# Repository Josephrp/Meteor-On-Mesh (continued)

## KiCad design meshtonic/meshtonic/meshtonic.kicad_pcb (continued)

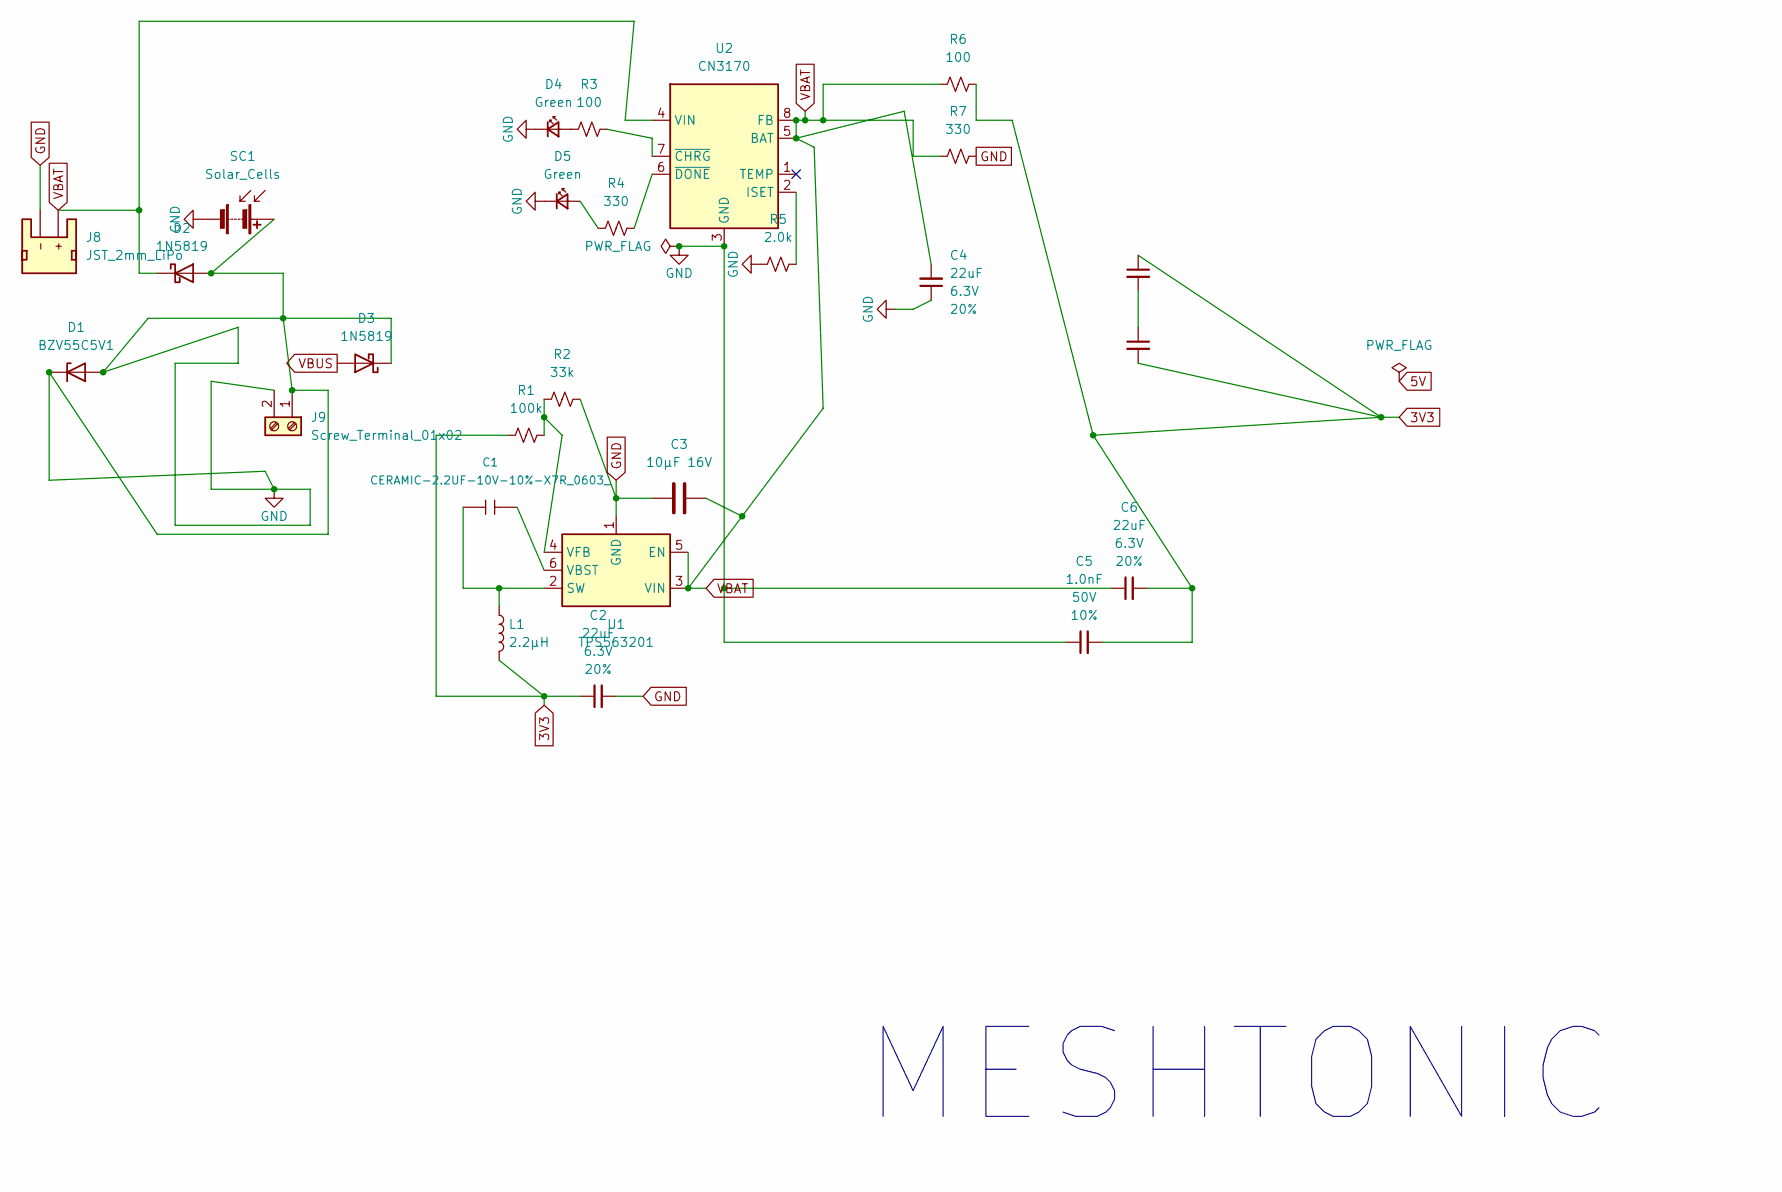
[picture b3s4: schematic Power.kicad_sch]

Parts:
C1: CERAMIC-2.2UF-10V-10%-X7R_0603_; C_0603_1608Metric; MPN CC0603KRX7R6BB225
C2, C4, C6, C7: 22uF; C_0603_1608Metric; Voltage 6.3V; Tolerance 20%
C3: 10µF 16V; C_0603_1608Metric
C5, C8: 1.0nF; C_0603_1608Metric; Voltage 50V; Tolerance 10%
D1: BZV55C5V1; D_MiniMELF
D2, D3: 1N5819; D_DO-41_SOD81_P10.16mm_Horizontal
D4, D5: Green; LED_1206_3216Metric_Green
J8: JST_2mm_LiPo; JST_1x02_P2.0mm_Horizontal_SMD
J9: Screw_Terminal_01x02; PinHeader_1x02_P2.54mm_Vertical
L1: 2.2µH; L_6.3x6.3_H3
R1: 100k; R_0402_1005Metric
R2: 33k; R_0402_1005Metric
R3, R6: 100; R_0402_1005Metric
R4, R7: 330; R_0603_1608Metric
R5: 2.0k; R_0402_1005Metric
SC1: Solar_Cells; PinHeader_1x02_P2.54mm_Vertical
U1: TPS563201; SOT-23-6
U2: CN3170; SOIC-8-1EP_3.9x4.9mm_P1.27mm_EP2.41x3.3mm_ThermalVias

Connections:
3V3: C2.1, C5.2, C6.2, C7.1, C8.2, L1.2, R1.1, R6.2; also elsewhere on the board
GND: C2.2, C3.1, C4.1, C5.1, C6.1, D1.1 (K), D1.2 (A), D2.2 (A), D3.1 (K), D4.1 (K), D5.1 (K), J8.1 (-), J9.1, J9.2, R2.2, R5.1, R7.2, SC1.1 (+), SC1.2 (-), U1.1 (GND), U2.3 (GND), U2.9 (GND); also elsewhere on the board
unnamed: C7.2, C8.1
unnamed: D4.2 (A), R3.1
unnamed: D5.2 (A), R4.1
unnamed: C1.2, L1.1, U1.2 (SW)
unnamed: C1.1, U1.6 (VBST)
unnamed: R1.2, R2.1, U1.4 (VFB)
unnamed: R5.2, U2.2 (ISET)
unnamed: R3.2, U2.7 (~CHRG)
unnamed: R4.2, U2.6 (~DONE)
VBAT: C3.2, C4.2, D2.1 (K), J8.2 (+), R6.1, R7.1, U1.3 (VIN), U1.5 (EN), U2.4 (VIN), U2.5 (BAT), U2.8 (FB); also elsewhere on the board
VBUS: D3.2 (A); also elsewhere on the board

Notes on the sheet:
MESHTONIC

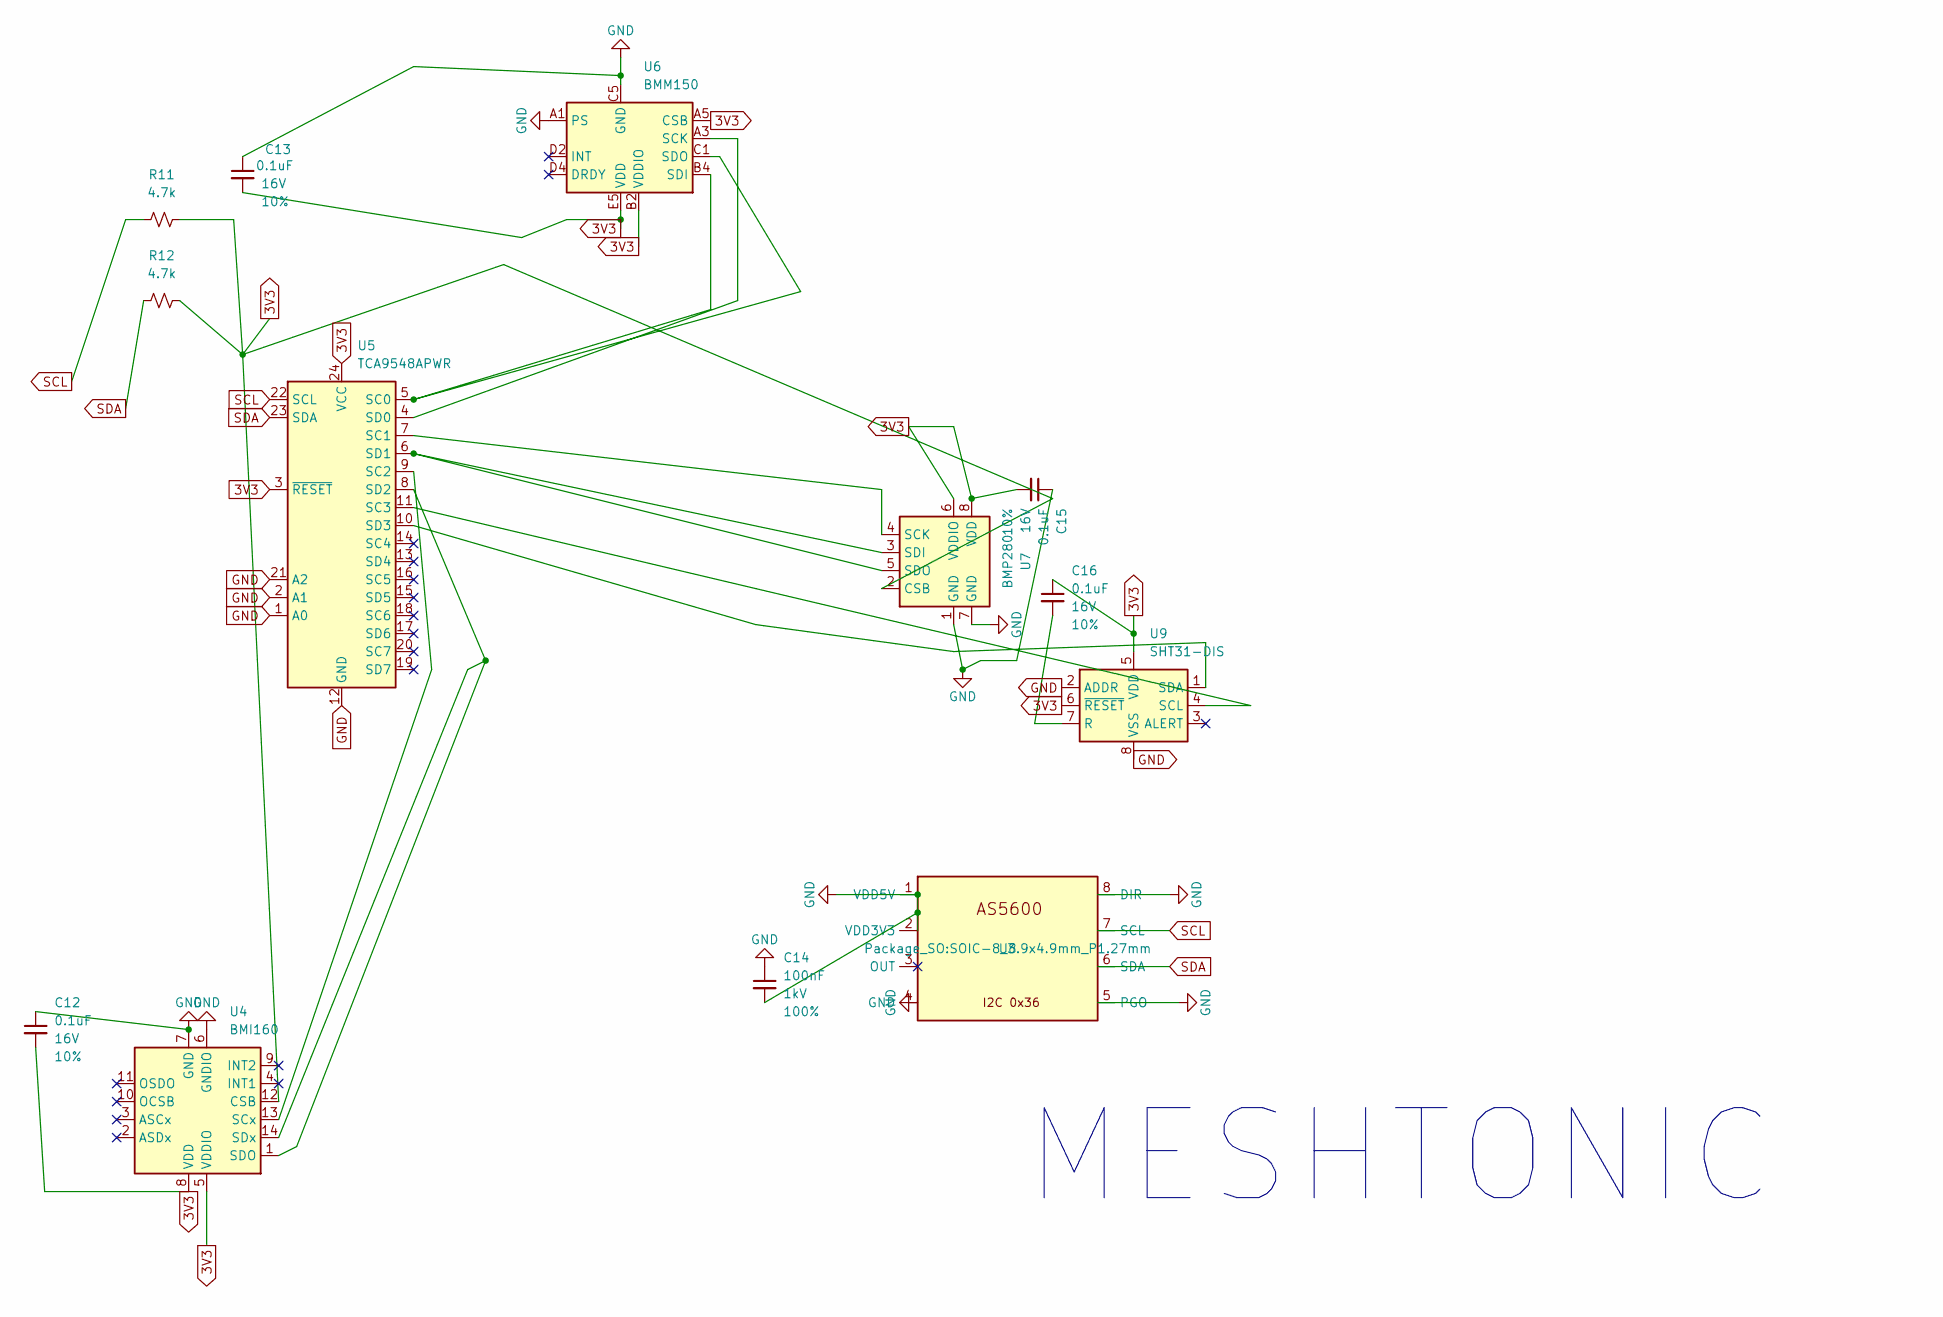
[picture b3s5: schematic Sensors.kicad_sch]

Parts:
C12, C13, C15, C16: 0.1uF; C_0402_1005Metric; Voltage 16V; Tolerance 10%
C14: 100nF; C_0603_1608Metric; Voltage 1kV; Tolerance 100%
R11, R12: 4.7k; R_0402_1005Metric
U4: BMI160; Bosch_LGA-14_3x2.5mm_P0.5mm
U5: TCA9548APWR; TSSOP-24_4.4x7.8mm_P0.65mm
U6: BMM150; WLCSP-12_1.56x1.56mm_P0.4mm
U7: BMP280; Bosch_LGA-8_2x2.5mm_P0.65mm_ClockwisePinNumbering
U8: Package_SO:SOIC-8_3.9x4.9mm_P1.27mm; SOIC-8_3.9x4.9mm_P1.27mm
U9: SHT31-DIS; Sensirion_DFN-8-1EP_2.5x2.5mm_P0.5mm_EP1.1x1.7mm

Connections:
3V3: C12.2, C13.2, C15.2, C16.1, R11.2, R12.2, U4.5 (VDDIO), U4.8 (VDD), U4.12 (CSB), U5.3 (~RESET), U5.24 (VCC), U6.A5 (CSB), U6.B2 (VDDIO), U6.E5 (VDD), U7.2 (CSB), U7.6 (VDDIO), U7.8 (VDD), U9.5 (VDD), U9.6 (~RESET); also elsewhere on the board
GND: C12.1, C13.1, C14.1, C14.2, C15.1, U4.6 (GNDIO), U4.7 (GND), U5.1 (A0), U5.2 (A1), U5.12 (GND), U5.21 (A2), U6.A1 (PS), U6.C5 (GND), U6.E1 (GND), U6.E3 (GND), U7.1 (GND), U7.7 (GND), U8.1 (VDD5V), U8.2 (VDD3V3), U8.4 (GND), U8.5 (PGO), U8.8 (DIR), U9.2 (ADDR), U9.8 (VSS), U9.9 (VSS); also elsewhere on the board
unnamed: U4.13 (SCx), U5.9 (SC2)
unnamed: U4.1 (SDO), U4.14 (SDx), U5.8 (SD2)
unnamed: U5.5 (SC0), U6.B4 (SDI), U6.C1 (SDO)
unnamed: U5.7 (SC1), U7.4 (SCK)
unnamed: U5.11 (SC3), U9.4 (SCL)
unnamed: U5.4 (SD0), U6.A3 (SCK)
unnamed: U5.6 (SD1), U7.3 (SDI), U7.5 (SDO)
unnamed: U5.10 (SD3), U9.1 (SDA)
unnamed: C16.2, U9.7 (R)
SCL: R11.1, U5.22 (SCL), U8.7 (SCL); also elsewhere on the board
SDA: R12.1, U5.23 (SDA), U8.6 (SDA); also elsewhere on the board

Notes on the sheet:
MESHTONIC

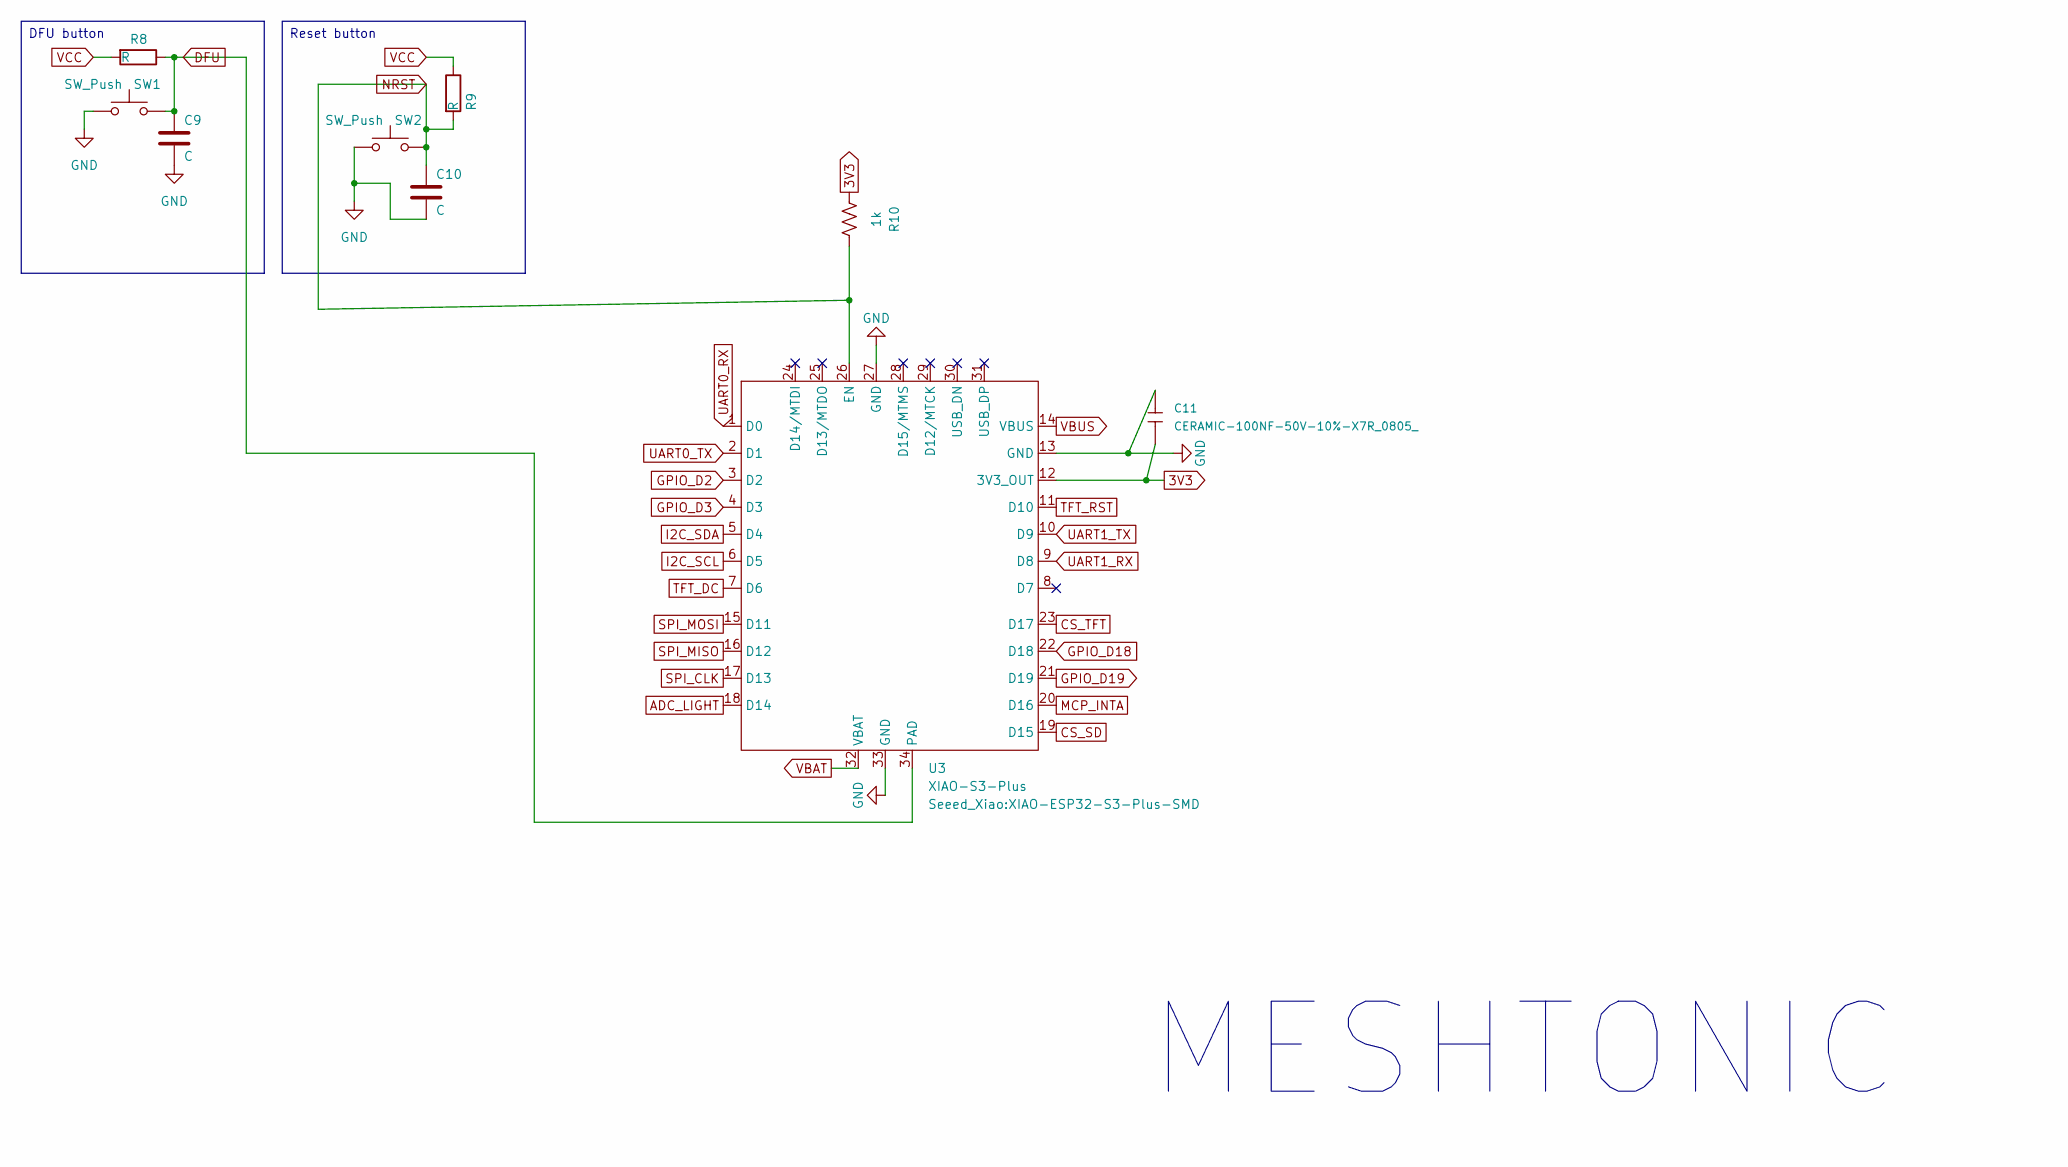
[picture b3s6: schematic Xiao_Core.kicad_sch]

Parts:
C9, C10: C; C_0402_1005Metric; Part CL05B104KO5NNNC; JLC 0402
C11: CERAMIC-100NF-50V-10%-X7R_0805_; C_0603_1608Metric; MPN CC0805KRX7R9BB104
R8, R9: R; R_0603_1608Metric; Part 0603WAF1103T5E; JLC 0603
R10: 1k; R_0603_1608Metric
SW1, SW2: SW_Push; SW_Push_1P1T_XKB_TS-1187A; Part TS-1187A-B-A-B; JLC SMD
U3: XIAO-S3-Plus; XIAO-ESP32-S3-Plus-SMD

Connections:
3V3: C11.2, R10.2, U3.12 (3V3_OUT); also elsewhere on the board
ADC_LIGHT: U3.18 (D14); also elsewhere on the board
CS_SD: U3.19 (D15); also elsewhere on the board
CS_TFT: U3.23 (D17); also elsewhere on the board
DFU: C9.1, R8.1, SW1.2, U3.34 (PAD)
GND: C9.2, C10.2, C11.1, SW1.1, SW2.1, U3.13 (GND), U3.27 (GND), U3.33 (GND); also elsewhere on the board
GPIO_D2: U3.3 (D2); also elsewhere on the board
GPIO_D3: U3.4 (D3); also elsewhere on the board
GPIO_D18: U3.22 (D18); also elsewhere on the board
GPIO_D19: U3.21 (D19); also elsewhere on the board
I2C_SCL: U3.6 (D5); also elsewhere on the board
I2C_SDA: U3.5 (D4); also elsewhere on the board
MCP_INTA: U3.20 (D16); also elsewhere on the board
NRST: C10.1, R9.2, R10.1, SW2.2, U3.26 (EN)
SPI_CLK: U3.17 (D13); also elsewhere on the board
SPI_MISO: U3.16 (D12); also elsewhere on the board
SPI_MOSI: U3.15 (D11); also elsewhere on the board
TFT_DC: U3.7 (D6); also elsewhere on the board
TFT_RST: U3.11 (D10); also elsewhere on the board
UART0_RX: U3.1 (D0); also elsewhere on the board
UART0_TX: U3.2 (D1); also elsewhere on the board
UART1_RX: U3.9 (D8); also elsewhere on the board
UART1_TX: U3.10 (D9); also elsewhere on the board
VBAT: U3.32 (VBAT); also elsewhere on the board
VBUS: U3.14 (VBUS); also elsewhere on the board
VCC: R8.2, R9.1

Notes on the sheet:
MESHTONIC
DFU button
Reset button

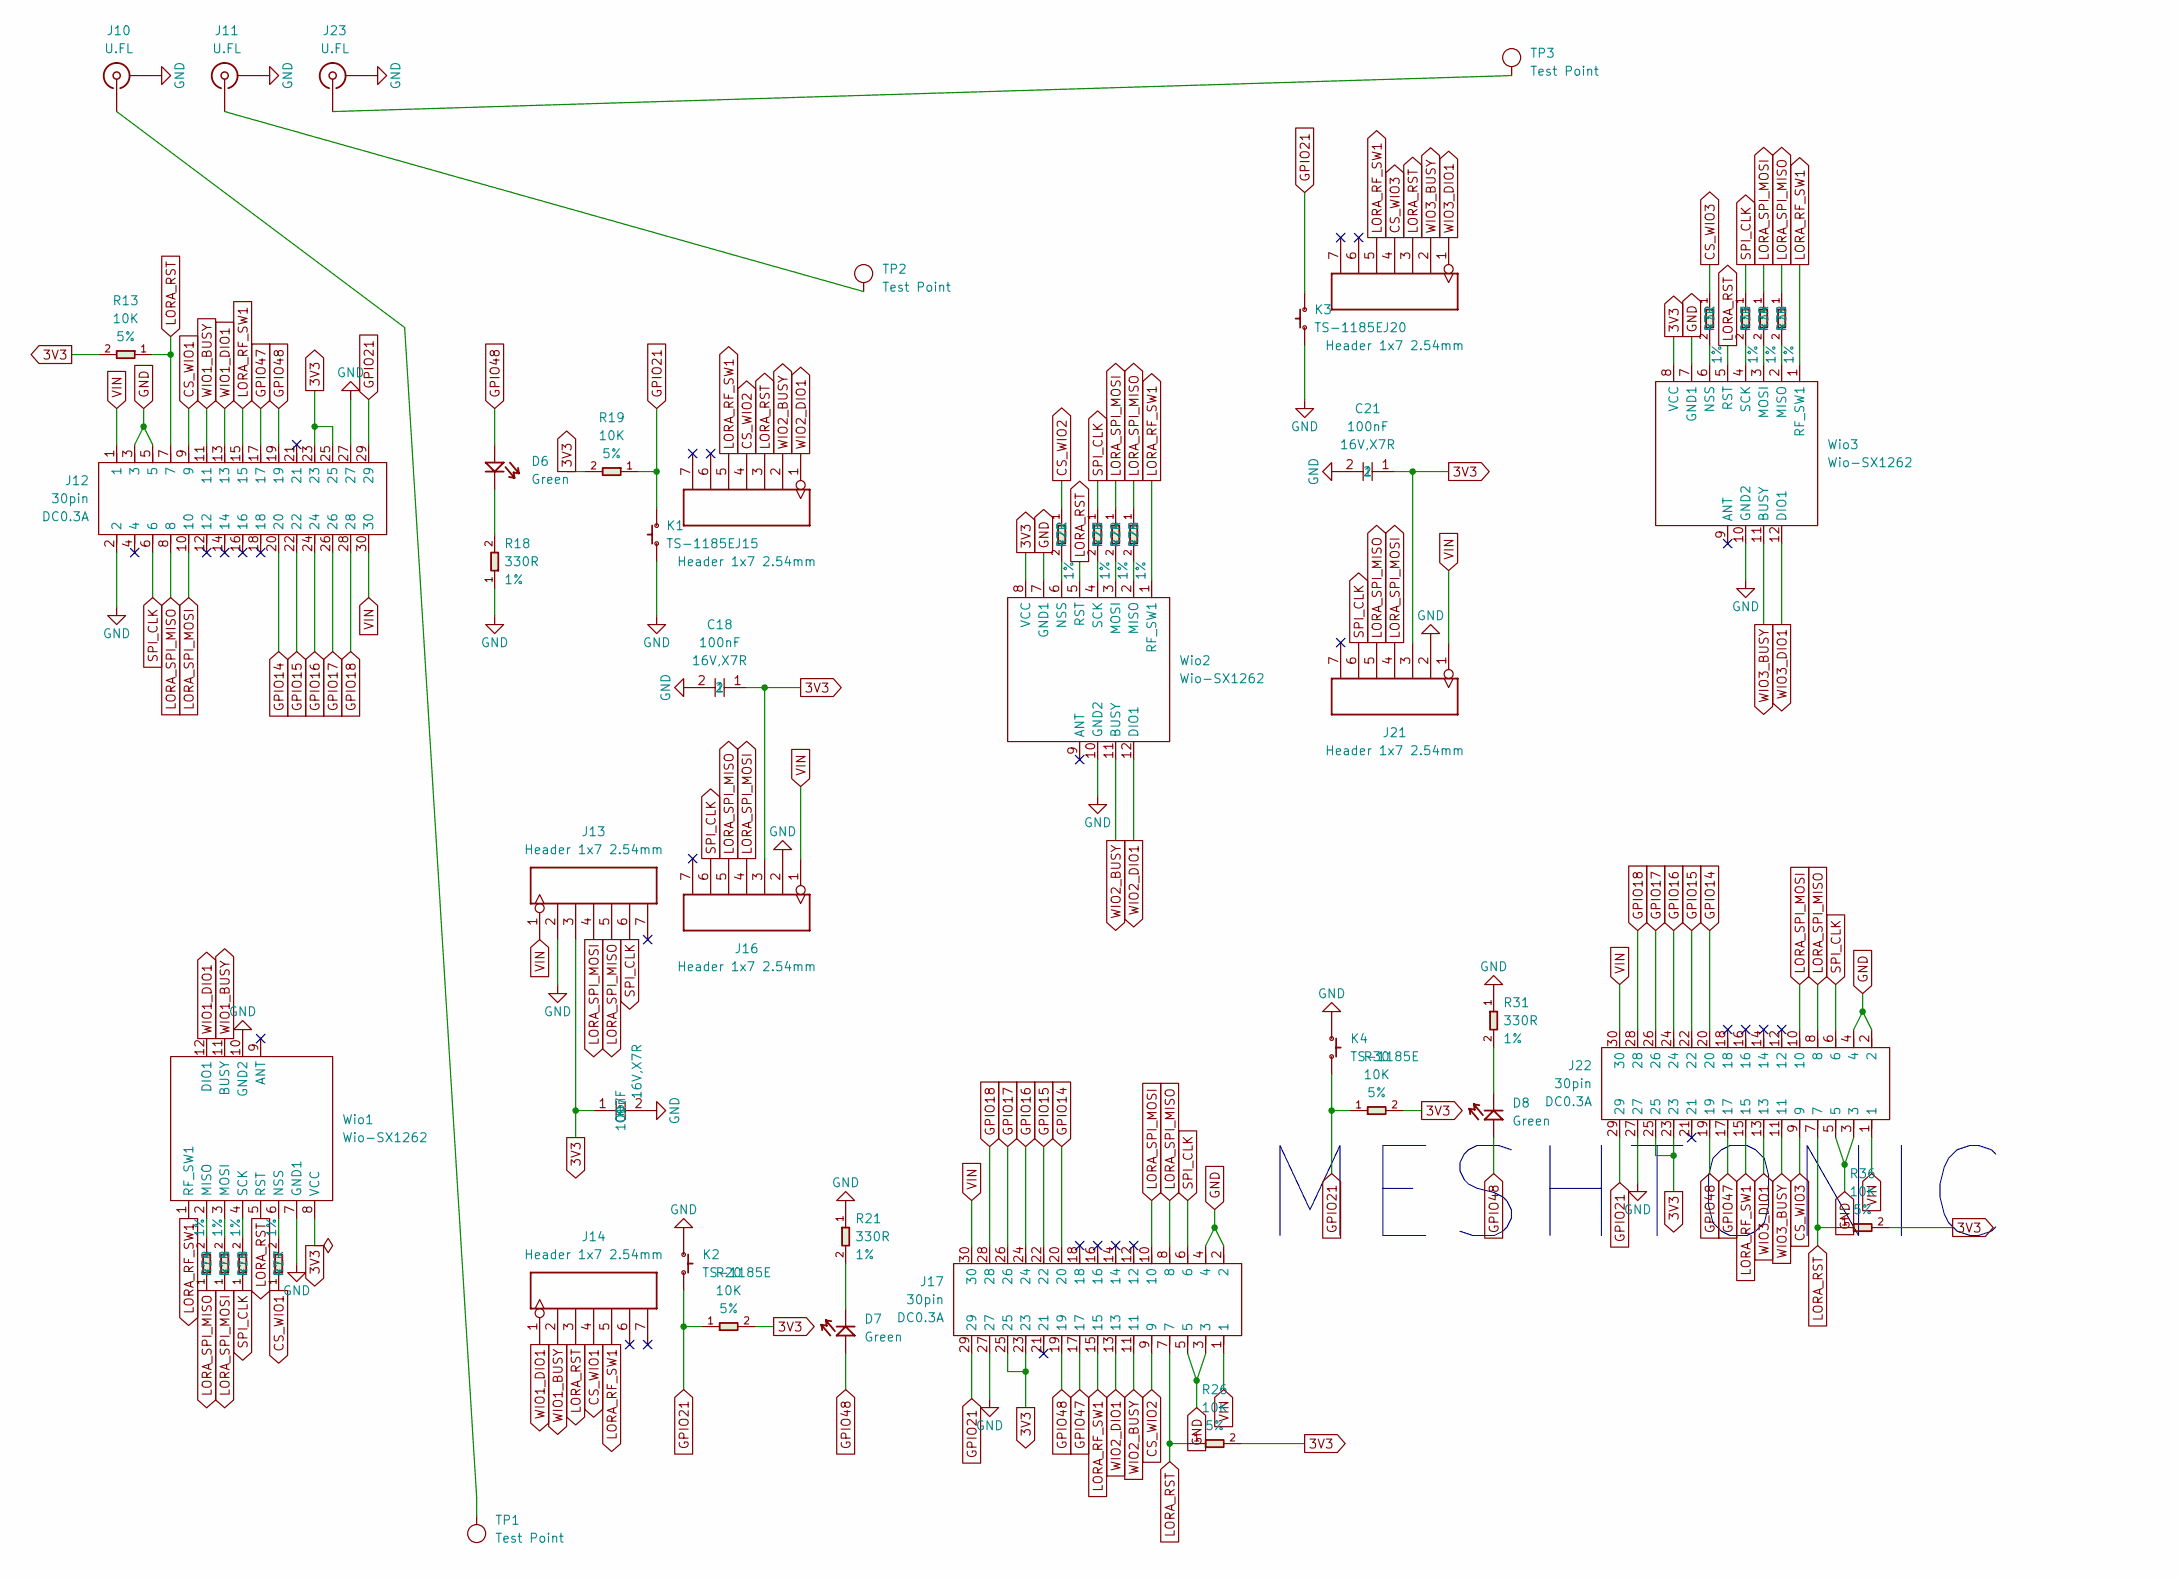
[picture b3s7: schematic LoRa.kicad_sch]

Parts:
C17, C18, C21: 100nF; C0402; Voltage Rating 16V,X7R; MPN CC0402KRX7R7BB104
D6: Green; D_0201_0603Metric; MPN 19-217/G7C-AN1P2/3T
D7, D8: Green; D_0603_1608Metric; MPN 19-217/G7C-AN1P2/3T
J10, J11, J23: U.FL
J12: 30pin; PinHeader_2x15_P2.54mm_Vertical; Rating DC0.3A; MPN BTB SCOKET P0.40
J13, J14, J15, J16, J20, J21: Header 1x7 2.54mm; PinHeader_1x07_P2.54mm_Vertical; Part Type Header
J17, J22: 30pin; PinSocket_2x15_P2.54mm_Vertical; Rating DC0.3A; MPN BTB SCOKET P0.40
K1, K2, K3, K4: TS-1185E; SW_SPST_TL3342; MPN TS-1185E
R13, R19, R20, R26, R30, R36: 10K; R0402; Power Rating 5%; MPN RC0402JR-0710KL
R14, R15, R16, R17, R22, R23, R24, R25, R32, R33, R34, R35: 47R; R0402; Power Rating 1%; MPN RC0201FR-0745RL
R18, R21, R31: 330R; R0402; Power Rating 1%; MPN RC0402FR-07330RL
TP1, TP2, TP3: Test Point; TP-D3_5c2_2mm; Part Type Test Point
Wio1, Wio2, Wio3: Wio-SX1262; Wio-SX1262-12P; MPN Wio-SX1262

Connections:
3V3: C17.1, C18.1, C21.1, J12.23, J12.25, J13.3, J16.3, J17.23, J17.25, J21.3, J22.23, J22.25, R13.2, R19.2, R20.2, R26.2, R30.2, R36.2, Wio1.8 (VCC), Wio2.8 (VCC), Wio3.8 (VCC); also elsewhere on the board
CS_WIO1: J12.9, J14.4, R17.1; also elsewhere on the board
CS_WIO2: J15.4, J17.9, R22.1; also elsewhere on the board
CS_WIO3: J20.4, J22.9, R32.1; also elsewhere on the board
GND: C17.2, C18.2, C21.2, J10.2 (Ext), J11.2 (Ext), J12.2, J12.3, J12.5, J12.27, J13.2, J16.2, J17.2, J17.3, J17.4, J17.5, J17.27, J21.2, J22.2, J22.3, J22.4, J22.5, J22.27, J23.2 (Ext), K1.1, K2.1, K3.1, K4.1, R18.1, R21.1, R31.1, Wio1.7 (GND1), Wio1.10 (GND2), Wio2.7 (GND1), Wio2.10 (GND2), Wio3.7 (GND1), Wio3.10 (GND2); also elsewhere on the board
GPIO21: J12.29, J17.29, J22.29, K1.2, K2.2, K3.2, K4.2, R19.1, R20.1, R30.1
GPIO48: D6.1 (+), D7.1 (+), D8.1 (+), J12.19, J17.19, J22.19
LORA_RF_SW1: J12.15, J14.5, J15.5, J17.15, J20.5, J22.15, Wio1.1 (RF_SW1), Wio2.1 (RF_SW1), Wio3.1 (RF_SW1)
LORA_RST: J12.7, J14.3, J15.3, J17.7, J20.3, J22.7, R13.1, R26.1, R36.1, Wio1.5 (RST), Wio2.5 (RST), Wio3.5 (RST)
LORA_SPI_MISO: J12.8, J13.5, J16.5, J17.8, J21.5, J22.8, R14.1, R25.1, R35.1
LORA_SPI_MOSI: J12.10, J13.4, J16.4, J17.10, J21.4, J22.10, R15.1, R24.1, R34.1
unnamed: D6.2 (-), R18.2
unnamed: D7.2 (-), R21.2
unnamed: D8.2 (-), R31.2
unnamed: J10.1 (In), TP1.1 (T_1)
unnamed: J11.1 (In), TP2.1 (T_1)
unnamed: J12.17, J17.17, J22.17
unnamed: J12.20, J17.20, J22.20
unnamed: J12.22, J17.22, J22.22
unnamed: J12.24, J17.24, J22.24
unnamed: J12.26, J17.26, J22.26
unnamed: J12.28, J17.28, J22.28
unnamed: J23.1 (In), TP3.1 (T_1)
unnamed: R14.2, Wio1.2 (MISO)
unnamed: R15.2, Wio1.3 (MOSI)
unnamed: R17.2, Wio1.6 (NSS)
unnamed: R16.2, Wio1.4 (SCK)
unnamed: R25.2, Wio2.2 (MISO)
unnamed: R24.2, Wio2.3 (MOSI)
unnamed: R22.2, Wio2.6 (NSS)
unnamed: R23.2, Wio2.4 (SCK)
unnamed: R35.2, Wio3.2 (MISO)
unnamed: R34.2, Wio3.3 (MOSI)
unnamed: R32.2, Wio3.6 (NSS)
unnamed: R33.2, Wio3.4 (SCK)
SPI_CLK: J12.6, J13.6, J16.6, J17.6, J21.6, J22.6, R16.1, R23.1, R33.1; also elsewhere on the board
VIN: J12.1, J12.30, J13.1, J16.1, J17.1, J17.30, J21.1, J22.1, J22.30
WIO1_BUSY: J12.11, J14.2, Wio1.11 (BUSY); also elsewhere on the board
WIO1_DIO1: J12.13, J14.1, Wio1.12 (DIO1); also elsewhere on the board
WIO2_BUSY: J15.2, J17.11, Wio2.11 (BUSY); also elsewhere on the board
WIO2_DIO1: J15.1, J17.13, Wio2.12 (DIO1); also elsewhere on the board
WIO3_BUSY: J20.2, J22.11, Wio3.11 (BUSY); also elsewhere on the board
WIO3_DIO1: J20.1, J22.13, Wio3.12 (DIO1); also elsewhere on the board

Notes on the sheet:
MESHTONIC

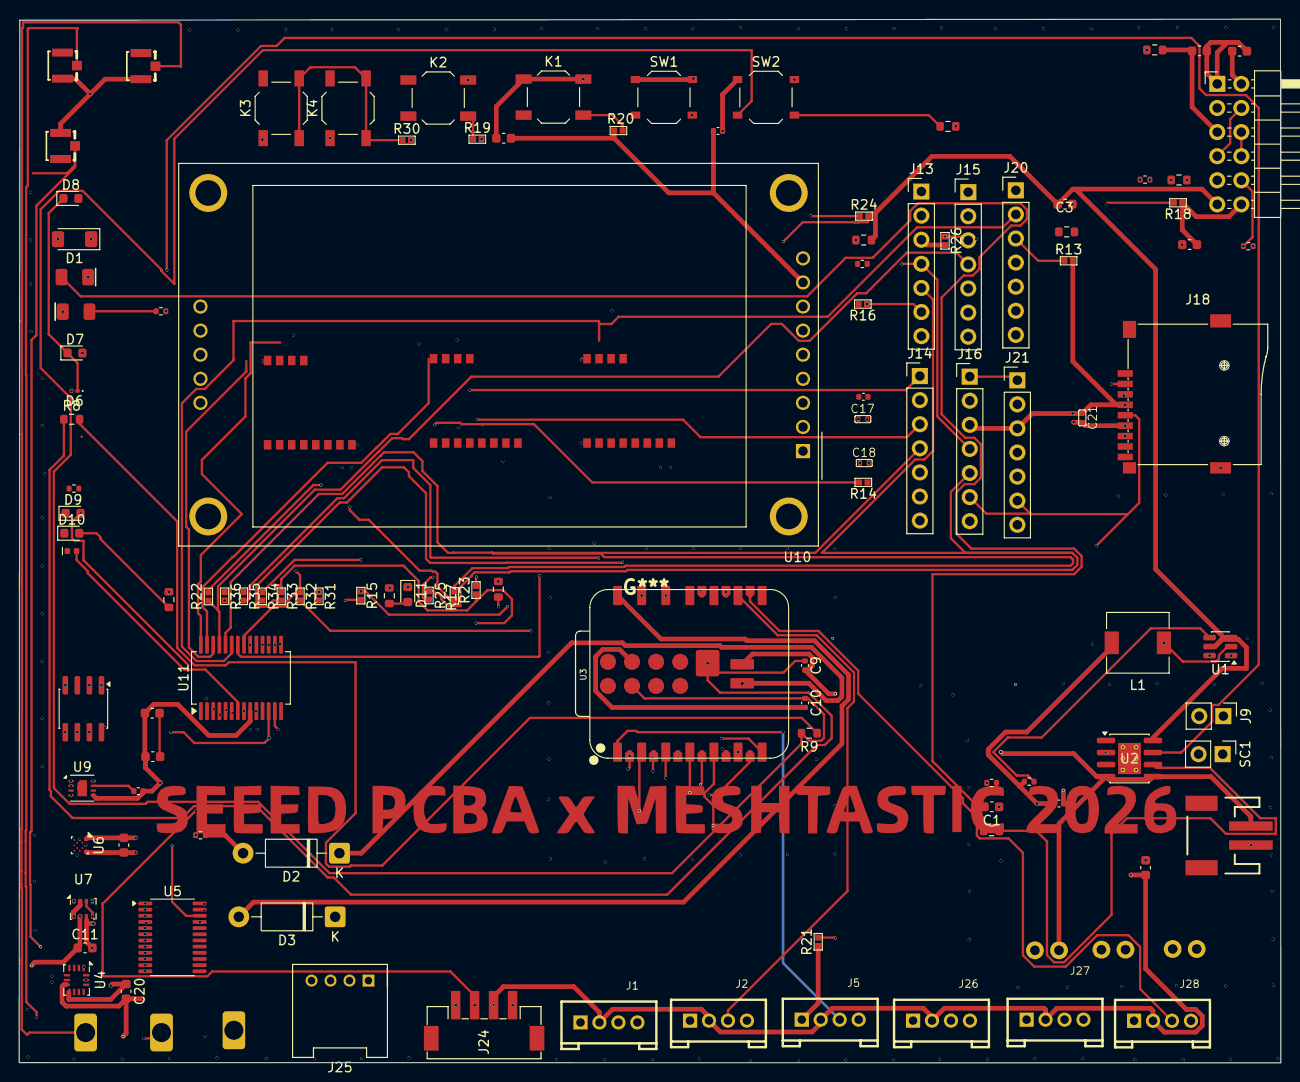
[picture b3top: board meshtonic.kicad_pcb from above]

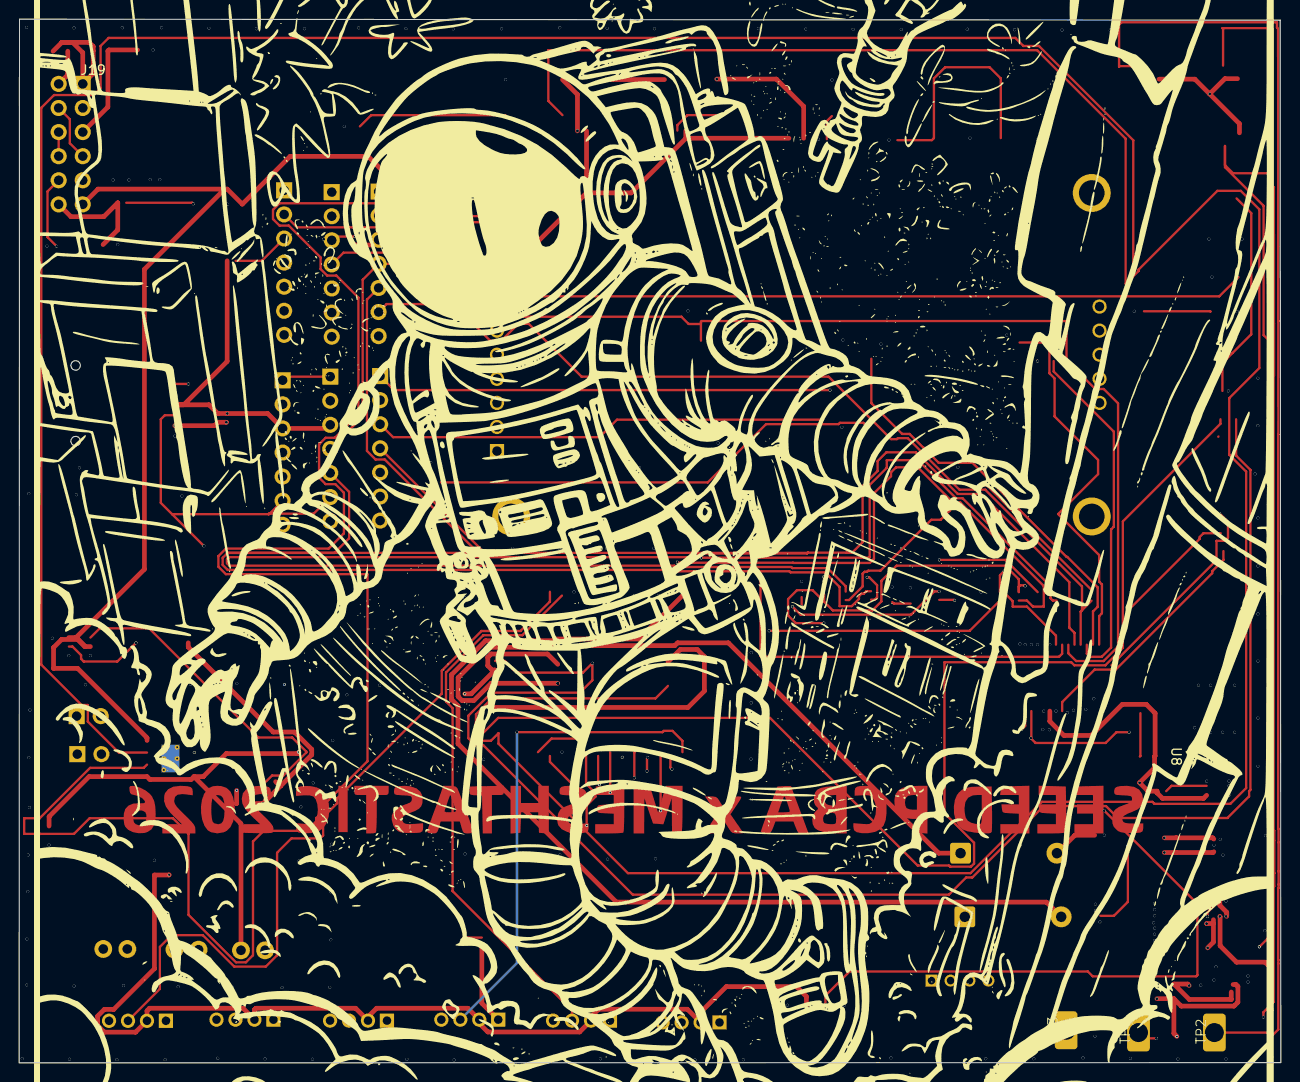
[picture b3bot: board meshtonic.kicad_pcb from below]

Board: 6 copper layers, 133.0 x 110.0 mm, 122 parts (3 on the bottom side), 93 nets.

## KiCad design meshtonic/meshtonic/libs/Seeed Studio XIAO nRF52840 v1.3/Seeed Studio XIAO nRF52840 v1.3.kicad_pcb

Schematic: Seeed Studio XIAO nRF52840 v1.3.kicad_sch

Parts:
ANT1: ANTENNA-AN3216; ANT-SMD3P-3.2X1.6X1.04MM
BAT0: TEST-POINT'4080'; TP-80X40MIL
C1, C5, C8, C24, C34: 100nF; C0201
C2, C7: 10pF; C0201
C3, C4, C6, C9, C22, C25, C29, C30, C39, C41, C42: 2.2uF; C0201
C10: 1nF; C0402
C11: 1pF; C0201
C31: 820pF; C0201
C32, C33: 15pF; C0201
C35: 100pF; C0201
C36: 0.8pF; C0201
C37: 0.5pF; C0201
C38: 4.7nH; L0201
C40: DNP; C0201
CHG0: RED; LED-0402
D1: DIODE'0603'; SOD-523
GND0: GND; TP-80X40MIL
J1, J2: DNP; H7-HALF-HOLE-2.54
K1: BUTTON-4P; SW4-SMD-2.8-2.6X1.6X0.53MM
L3: 10uH; L0603
MIC1: MSM261D3526H1CPM; MIC6P-3.5X2.65X0.94MM
NFC1, NFC2: TEST-POINT'4080'; TP-80X40MIL
Q1: PMOS_1.00.60.35MM; PMOS_1.0_0.6_0.35MM
R1, R2: 5.1k; R0201
R3, R5, R7: 2.2k; R0201
R4, R13, R14, R15, R20: 10k; R0201
R9: 100k; R0201
R10, R11: 33R; R0201
R12, R18: 2.7k; R0201
R16: 1M_1%; R0201
R17: 510k_1%; R0201
RGB6: RGB; 4P1010
TP1, TP2, TP3, TP5: TEST-POINT'4545'; TP-D45MIL
U1: NRF52840_QF; AQFN50P700X700X85_HS-74N
U2: BQ25100; BQ25101_DSBGA_6_BQ25101
U3: LSM6DS3TR-C; LGA14-0.5-2.5X3X0.86MM
U6: 3.3V; X2SON-4
U7: DNP; USON2X3_8
USB1: USB2.0-TYPE-C
X1: 32.768KHz; X2-SMD-L1.6X1.0X0.5MM
X2: 32MHz; 4P1612

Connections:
3V3: C3.2, C6.2, C29.2, C39.1, C41.2, J1.5, J1.17 (5), R5.1, R13.1, RGB6.+, U1.A22 (VDD@A22), U1.AD14 (VDD@AD14), U1.AD23 (VDD@AD23), U1.B1 (VDD@B1), U1.W1 (VDD@W1), U1.Y2 (VDDH@Y2), U6.1 (OUT), U7.8 (VCC)
6D_INT1: U1.T2 (P0.11@T2), U3.4 (INT1)
6D_PWR: C1.2, R14.1, R15.1, U1.P2 (P1.08@P2), U3.5 (VDDIO), U3.8 (VDD), U3.12 (CS)
/CE: R20.1, U2.B1 (TS)
DEC4-6: C34.1, C42.1, L3.2, U1.B5 (DEC4@B5), U1.E24 (DEC6@E24)
GND: ANT1.2 (GND), C1.1, C2.1, C3.1, C4.2, C5.2, C6.1, C7.1, C8.1, C9.1, C10.2, C11.1, C22.1, C24.1, C25.1, C29.1, C30.2, C31.2, C32.2, C33.2, C34.2, C35.2, C36.1, C37.1, C39.2, C40.2, C41.1, C42.2, GND0.1, J1.6, J1.18 (6), K1.2 (B0), K1.4 (B1), MIC1.4 (GND@1), MIC1.5 (L/R), MIC1.6 (GND@2), R1.2, R2.1, R9.1, R18.2, R20.2, TP1.T, U1.B7 (VSS@B7), U1.F23 (VSS_PA@F23), U1.G74 (VSS_PAD), U2.C2 (VSS), U3.1 (SDO/DA0), U3.2 (SDX), U3.3 (SCX), U3.6 (GND@1), U3.7 (GND@2), U6.2 (GND), U6.T (GND), U7.4 (GND), U7.PAD (T), USB1.A1_B12 (A1/B12/GND), USB1.B1_A12 (B1/A12/GND), USB1.S1, USB1.S2, USB1.S3, USB1.S4, USB1.S5 (S1), USB1.S6 (S2), X2.2 (1), X2.4 (3)
INTERNAL_I2C_SCL: R14.2, U1.H2 (P0.27@H2), U3.13 (SCL)
INTERNAL_I2C_SDA: R15.2, U1.M2 (P0.07@M2), U3.14 (SDA)
unnamed: R1.1, USB1.A5 (A5/CC1)
unnamed: R2.2, USB1.B5 (B5/CC2)
unnamed: C2.2, U1.D2 (P0.00/XL1@D2), X1.2
unnamed: C7.2, U1.F2 (P0.01/XL2@F2), X1.1
unnamed: R7.1, RGB6.R-
unnamed: R4.1, RGB6.G-
unnamed: R10.2, U1.AD4 (D-@AD4)
unnamed: R11.2, U1.AD6 (D+@AD6)
unnamed: R3.1, RGB6.B-
unnamed: CHG0.+, R5.2
unnamed: ANT1.3, C10.1
unnamed: R12.1, R18.1, U2.B2 (ISET)
unnamed: C22.2, U1.AC5 (DECUSB@AC5)
unnamed: C24.2, U1.C1 (DEC1@C1)
unnamed: C31.1, U1.N24 (DEC5@N24)
unnamed: C33.1, U1.B24 (XC1@B24), X2.1 (2)
unnamed: C32.1, U1.A23 (XC2@A23), X2.3 (4)
unnamed: C35.1, U1.D23 (DEC3@D23)
unnamed: C36.2, C38.1, U1.H23 (ANT@H23)
unnamed: ANT1.1 (S), C37.2, C38.2
unnamed: C40.1, U1.A18 (DEC2@A18)
unnamed: L3.1, U1.B3 (DCC@B3)
P0.02_AIN0_LOW_A0_D0: J2.1, J2.13 (1), U1.A12 (P0.02/AIN0@A12)
P0.03_AIN1_LOW_A1_D1: J2.2, J2.14 (2), U1.B13 (P0.03/AIN1@B13)
P0.04_AIN2_A4_D4: J2.5, J2.17 (5), U1.J1 (P0.04/AIN2@J1)
P0.05_AIN3_A5_D5: J2.6, J2.18 (6), U1.K2 (P0.05/AIN3@K2)
P0.06_USER_BLUE: R3.2, U1.L1 (P0.06@L1)
P0.09/NFC1: NFC1.1, U1.L24 (P0.09/NFC1@L24)
P0.10/NFC2: NFC2.1, U1.J24 (P0.10/NFC2@J24)
P0.13_HICHG: R12.2, U1.AD8 (P0.13@AD8)
P0.14_~READ_BAT: R17.2, U1.AC9 (P0.14@AC9)
P0.16_PDM_DATA: MIC1.3 (DATA), U1.AC11 (P0.16@AC11)
P0.17_~CHG: CHG0.-, U1.AD12 (P0.17@AD12), U2.C1 (PRETERM)
P0.20_QSPI_SIO_0: U1.AD16 (P0.20@AD16), U7.5 (DI)
P0.21_QSPI_SCK: C11.2, U1.AC17 (P0.21@AC17), U7.6 (CLK)
P0.22_QSPI_SIO_2: U1.AD18 (P0.22@AD18), U7.3 (~WP)
P0.23_QSPI_SIO_3: U1.AC19 (P0.23@AC19), U7.7 (~HOLD)
P0.24_QSPI_SIO_1: U1.AD20 (P0.24@AD20), U7.2 (DO)
P0.25_QSPI_CSN: U1.AC21 (P0.25@AC21), U7.1 (~CS)
P0.26_USER_RED: R7.2, U1.G1 (P0.26@G1)
P0.28_AIN4_LOW_A2_D2: J2.3, J2.15 (3), U1.B11 (P0.28/AIN4@B11)
P0.29_AIN5_LOW_A3_D3: J2.4, J2.16 (4), U1.A10 (P0.29/AIN5@A10)
P0.30_USER_GREEN: R4.2, U1.B9 (P0.30/AIN6@B9)
P0.31_AIN7_BAT: R16.2, R17.1, U1.A8 (P0.31/AIN7@A8)
P1.00_PDM_CLK: MIC1.2 (CLK), U1.AD22 (P1.00@AD22)
P1.10_MIC_PWR: C8.2, MIC1.1 (VDD), U1.A20 (P1.10@A20)
P1.11_TX_D6: J2.7, J2.19 (7), U1.B19 (P1.11@B19)
P1.12_RX_D7: J1.1, J1.13 (1), U1.B17 (P1.12@B17)
P1.13_SCK_D8: J1.2, J1.14 (2), U1.A16 (P1.13@A16)
P1.14_MISO_D9: J1.3, J1.15 (3), U1.B15 (P1.14@B15)
P1.15_MOSI_D10: J1.4, J1.16 (4), U1.A14 (P1.15@A14)
PWR_LED: U1.R24 (P1.06@R24)
RESET: C5.1, K1.1 (A0), K1.3 (A1), R13.2, TP2.T, U1.AC13 (P0.18/RESET@AC13)
SWDCLK: TP3.T, U1.AA24 (SWDCLK@AA24)
SWDIO: TP5.T, U1.AC24 (SWDIO@AC24)
USB_D+: R11.1, USB1.A6 (A6/DP1), USB1.B6 (B6/DP2)
USB_D-: R10.1, USB1.A7 (A7/DN1), USB1.B7 (B7/DN2)
VBAT: BAT0.1, C30.1, Q1.1 (D), R16.1, U2.A1 (OUT)
VBUS: C9.2, C25.2, D1.+, J1.7, J1.19 (7), Q1.2 (G), R9.2, U1.AD2 (VBUS@AD2), U2.A2 (IN), USB1.A4_B9 (A4/B9/VBUS), USB1.B4_A9 (B4/A9/VBUS)
VIN: C4.1, D1.-, Q1.3 (S), U6.3 (EN), U6.4 (IN)

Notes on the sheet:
Linus.Liao
2.Change C32,C33 to 15pF
zhihuai.Zhou
Initail Version
the TS and VSS.
NTC:
2021.2.2
Set P0.14 to output Sink only to enable BAT voltage read;
v1.0
2.Add C11 to to resolve the issue of data corruption during Flash read operations.
1.Change 32M Crystal
Disable Temp sense function,
2025.6.20
1.Remove R8
use fixed 10k resistor between
2024.3.19

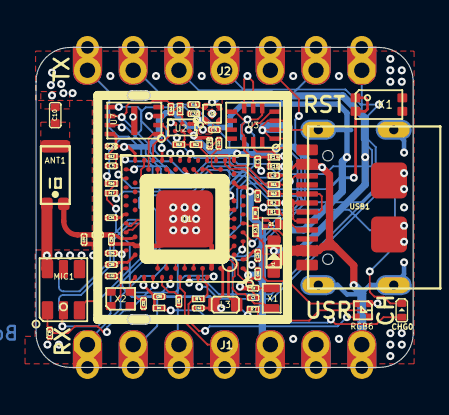
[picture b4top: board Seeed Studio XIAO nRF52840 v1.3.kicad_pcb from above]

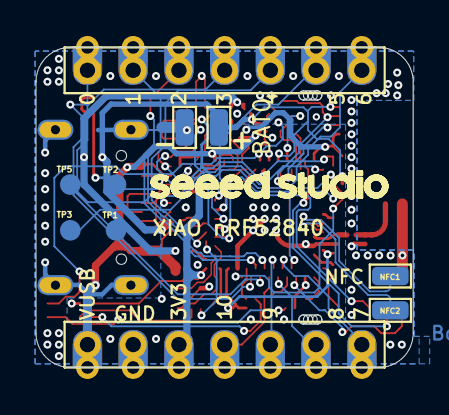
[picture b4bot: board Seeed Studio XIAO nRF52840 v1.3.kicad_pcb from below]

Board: 2 copper layers, 21.0 x 17.8 mm, 80 parts (9 on the bottom side), 67 nets.

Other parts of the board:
U$14: LOGO-SEEED-NEW-1_3X13MM
UNK_HOLE_0: dummyfp0
UNK_HOLE_1: dummyfp1
UNK_HOLE_2: dummyfp2
UNK_HOLE_3: dummyfp3
UNK_HOLE_4: dummyfp4
UNK_HOLE_5: dummyfp5
UNK_HOLE_6: dummyfp6
UNK_HOLE_7: dummyfp7
